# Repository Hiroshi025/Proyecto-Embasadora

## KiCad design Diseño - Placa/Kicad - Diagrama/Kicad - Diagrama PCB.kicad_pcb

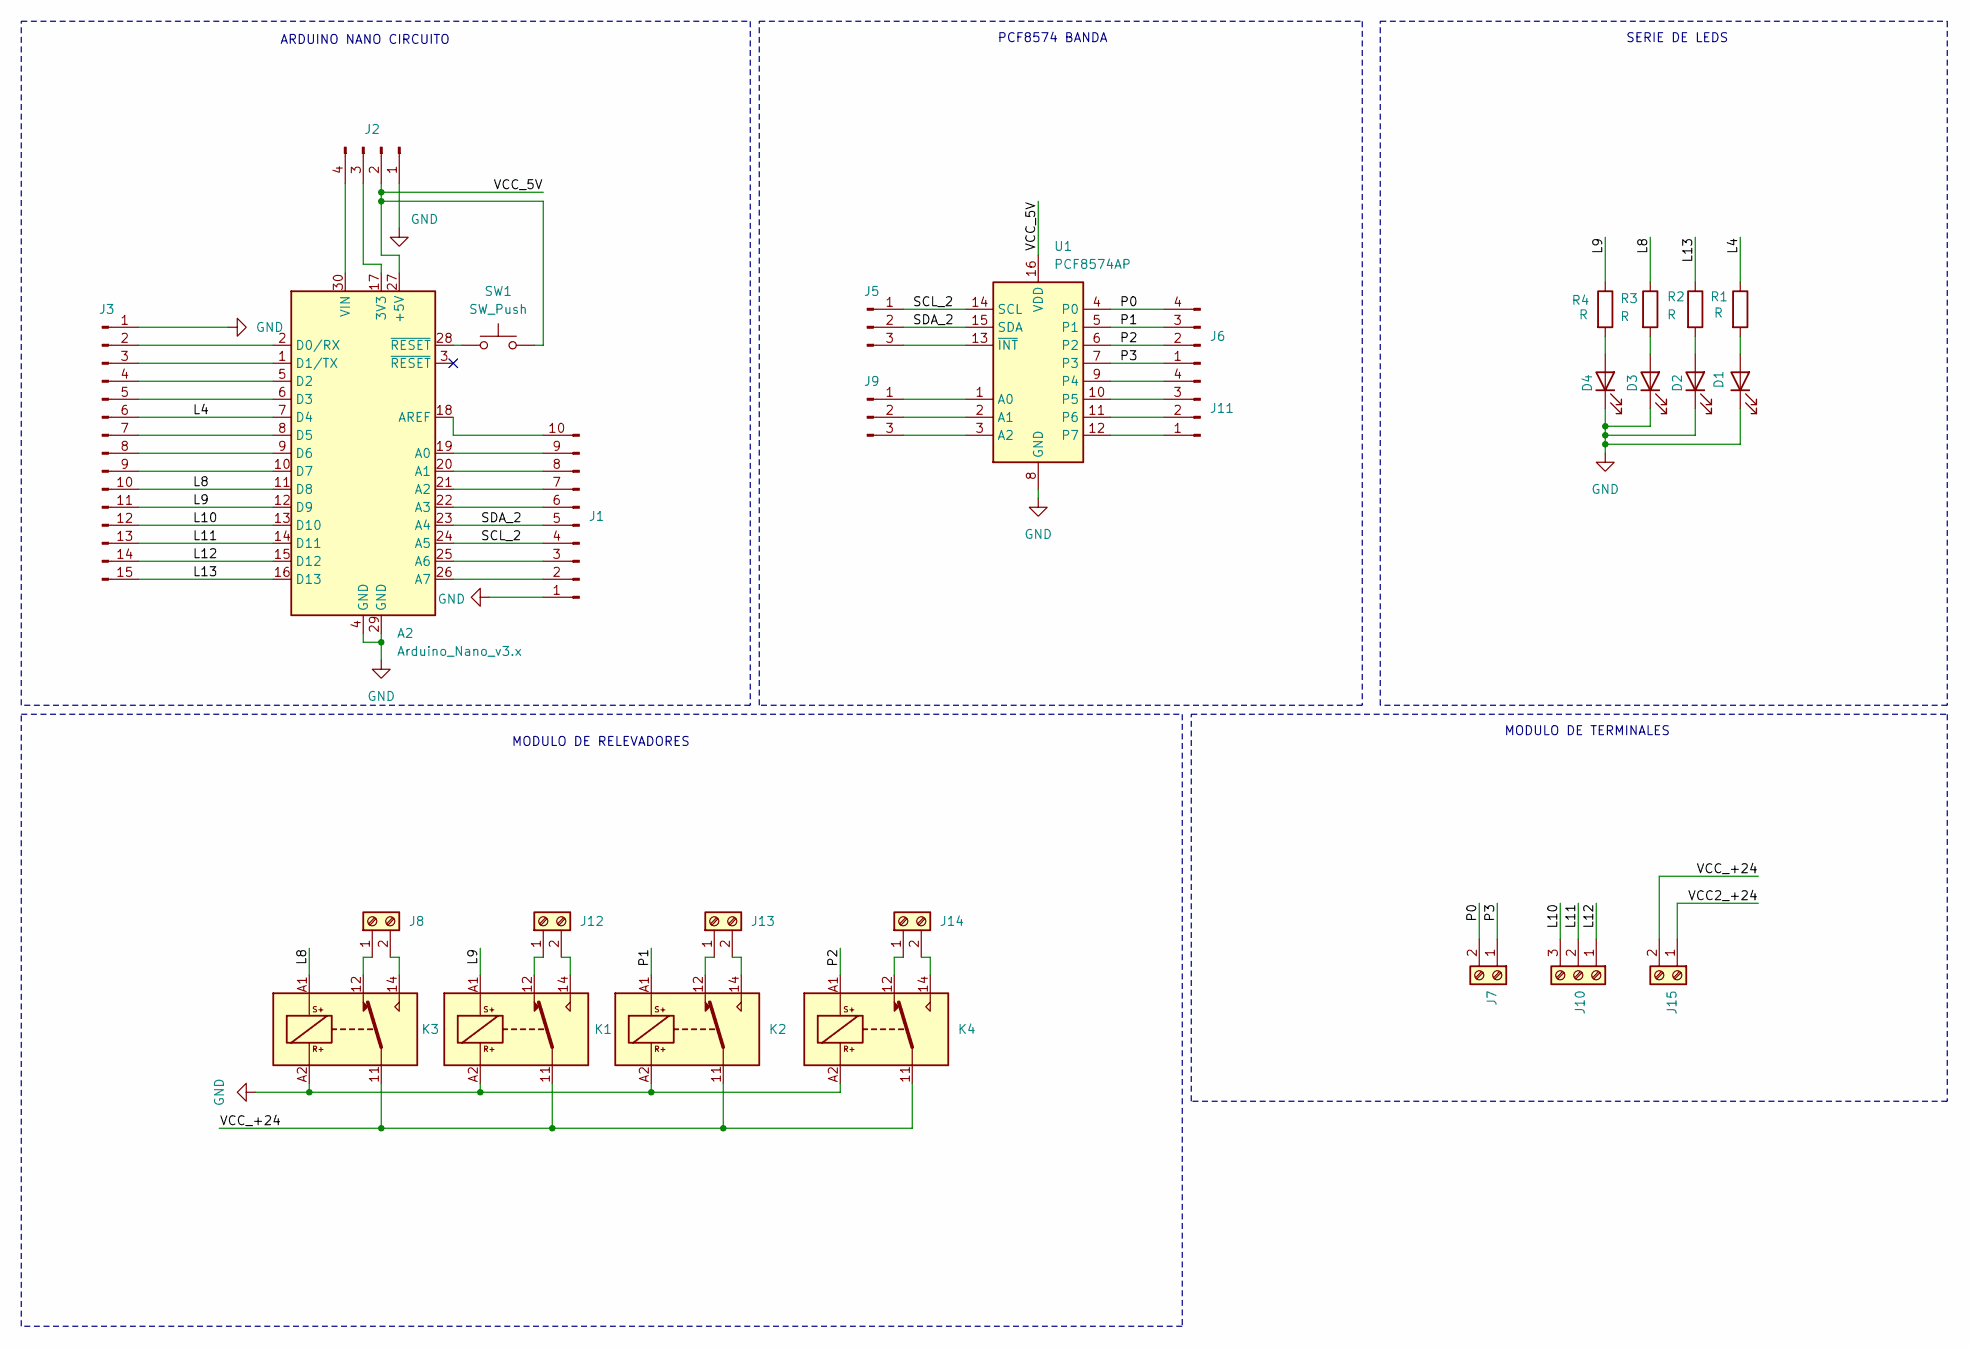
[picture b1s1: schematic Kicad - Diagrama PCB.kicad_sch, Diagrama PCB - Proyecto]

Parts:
A2: Arduino_Nano_v3.x; Arduino_Nano
D1, D2, D3, D4: LED; LED_D4.0mm
J1: Conn_01x10_Pin; PinHeader_1x10_P2.54mm_Vertical
J2, J6, J11: Conn_01x04_Pin; PinHeader_1x04_P2.54mm_Vertical
J3: Conn_01x15_Pin; PinHeader_1x15_P2.54mm_Vertical
J5, J9: Conn_01x03_Pin; PinHeader_1x03_P2.54mm_Vertical
J7, J8, J12, J13, J14, J15: Screw_Terminal_01x02; TerminalBlock_bornier-2_P5.08mm
J10: Screw_Terminal_01x03; TerminalBlock_bornier-3_P5.08mm
K1, K2, K3, K4: Relay_SPDT_Latching_1coil; Relay_SPDT_Finder_36.11
R1, R2, R3, R4: R; R_Axial_DIN0309_L9.0mm_D3.2mm_P15.24mm_Horizontal
SW1: SW_Push; SW_PUSH_6mm
U1: PCF8574AP; DIP-16_W7.62mm

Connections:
/L4: A2.7 (D4), J3.6, R1.1
/L8: A2.11 (D8), J3.10, K3.A1, R3.1
/L9: A2.12 (D9), J3.11, K1.A1, R4.1
/L10: A2.13 (D10), J3.12, J10.3
/L11: A2.14 (D11), J3.13, J10.2
/L12: A2.15 (D12), J3.14, J10.1
/L13: A2.16 (D13), J3.15, R2.1
/P0: J6.4, J7.2, U1.4 (P0)
/P1: J6.3, K2.A1, U1.5 (P1)
/P2: J6.2, K4.A1, U1.6 (P2)
/P3: J6.1, J7.1, U1.7 (P3)
/SCL_2: A2.24 (A5), J1.4, J5.1, U1.14 (SCL)
/SDA_2: A2.23 (A4), J1.5, J5.2, U1.15 (SDA)
/VCC2_+24: J15.1
/VCC_5V: A2.27 (+5V), J2.2, SW1.2, U1.16 (VDD)
/VCC_+24: J15.2, K1.11, K2.11, K3.11, K4.11
GND: A2.4 (GND), A2.29 (GND), D1.1 (K), D2.1 (K), D3.1 (K), D4.1 (K), J1.1, J2.1, J3.1, K1.A2, K2.A2, K3.A2, K4.A2, U1.8 (GND)
unnamed: A2.17 (3V3), J2.3
unnamed: A2.19 (A0), J1.9
unnamed: A2.20 (A1), J1.8
unnamed: A2.21 (A2), J1.7
unnamed: A2.22 (A3), J1.6
unnamed: A2.25 (A6), J1.3
unnamed: A2.26 (A7), J1.2
unnamed: A2.18 (AREF), J1.10
unnamed: A2.2 (D0/RX), J3.2
unnamed: A2.1 (D1/TX), J3.3
unnamed: A2.5 (D2), J3.4
unnamed: A2.6 (D3), J3.5
unnamed: A2.8 (D5), J3.7
unnamed: A2.9 (D6), J3.8
unnamed: A2.10 (D7), J3.9
unnamed: A2.30 (VIN), J2.4
unnamed: A2.28 (~RESET), SW1.1
unnamed: D1.2 (A), R1.2
unnamed: D2.2 (A), R2.2
unnamed: D3.2 (A), R3.2
unnamed: D4.2 (A), R4.2
unnamed: J5.3, U1.13 (~INT)
unnamed: J8.1, K3.12
unnamed: J8.2, K3.14
unnamed: J9.1, U1.1 (A0)
unnamed: J9.2, U1.2 (A1)
unnamed: J9.3, U1.3 (A2)
unnamed: J11.1, U1.12 (P7)
unnamed: J11.2, U1.11 (P6)
unnamed: J11.3, U1.10 (P5)
unnamed: J11.4, U1.9 (P4)
unnamed: J12.1, K1.12
unnamed: J12.2, K1.14
unnamed: J13.1, K2.12
unnamed: J13.2, K2.14
unnamed: J14.1, K4.12
unnamed: J14.2, K4.14

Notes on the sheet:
MODULO DE TERMINALES
SERIE DE LEDS
ARDUINO NANO CIRCUITO
PCF8574 BANDA
MODULO DE RELEVADORES

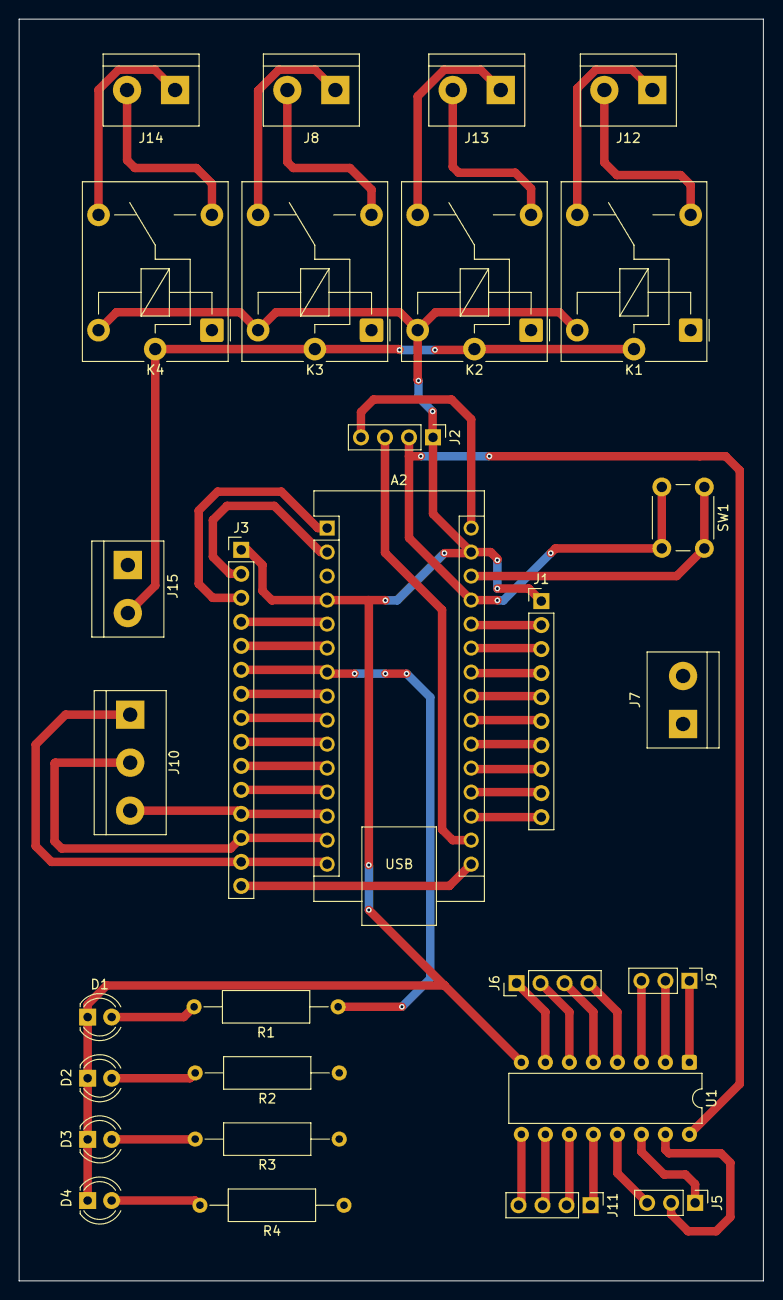
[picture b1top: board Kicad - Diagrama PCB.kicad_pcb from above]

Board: 4 copper layers, 78.8 x 133.5 mm, 29 parts (0 on the bottom side), 53 nets.

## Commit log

2025-06-30 Create
2025-06-30 Remove Fix
